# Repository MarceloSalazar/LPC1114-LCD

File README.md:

# LPC1114-LCD

Placa basada en el microcontrolador **NXP LPC1114FN28 (ARM Cortex-M0, DIP-28)** con pantalla **LCD 1602**, LEDs,
pulsadores y buzzer. Su uso principal es un **temporizador Pomodoro**, aunque también sirve como reloj con alarma.
Se programa en C.

**Esquemático:** [docs/hardware/LPC1114-LCD_schematic.pdf](docs/hardware/LPC1114-LCD_schematic.pdf)

| Fase | Contenido | Estado |
|------|-----------|--------|
| 1 | Hardware v1.2: PCB de 2 capas montado por JLCPCB (PCBA) con componentes Basic | Listo para fabricar |
| 1b | Caja impresa en 3D de dos piezas (FreeCAD) | Lista: STEP + STL en [enclosure/](enclosure) |
| 2 | Firmware en C: temporizador Pomodoro / reloj (+ tests) | Pendiente |

## Características (v1.2)

- **MCU**: LPC1114FN28/102, 50 MHz, 32 kB flash, 4 kB RAM, en zócalo DIP-28. La base de tiempos es un cristal de 12 MHz de ±10 ppm.
- **Alimentación**: micro USB (5 V) con protección ESD USBLC6-2SC6 y regulador XC6206 de 3,3 V.
  Si no montas el USBLC6, puenteas con estaño **JP3** y **JP4**.
- **USB-serie**: CH340C en el mismo conector micro USB. Además, pads UART de 1 × 3 (GND, RX, TX) a 3,3 V.
  Con los puentes **JP5** y **JP6** eliges si la UART del MCU va al CH340 (de fábrica) o a J3.
- **Programación**: pads de 1 × 7 (3V3, SWDIO, SWCLK, RESET, GND, SCL, SDA) para un programador CMSIS-DAP.
  Los pines SCL y SDA quedan libres para módulos I2C. También se puede programar con el bootloader ISP por UART,
  de forma automática si se cierran los puentes JP1 y JP2.
- **LCD 1602** en modo 4 bits, montado encima del PCB. El footprint es de 18 pines: 16 estándar más 2 para módulos RGB.
  La retroiluminación se regula por PWM y el contraste con un trimmer multivuelta.
- **Interfaz de usuario**: 4 pulsadores (MODE/ISP, UP, DOWN, OK), RESET, 3 LEDs y LED de encendido,
  y buzzer piezoeléctrico TDK PS1420P02CT.
- **RTC opcional (DNP)**: la cara inferior tiene la huella de un DS3231MZ, su condensador y un portapilas CR2032 SMD, en el bus I2C de J2.
  No se montan; quedan para una ampliación futura.
- **PCB**: **80 × 52 mm**, 2 capas. JLCPCB monta todos los componentes SMD (una sola cara, casi todos Basic).
  Tú sueldas 7 componentes: el LPC1114, el LCD, el trimmer, el buzzer, el USBLC6 y las 2 tiras de pines.

## Estructura del repositorio

```
LPC1114-LCD/
├── hardware/                 Proyecto KiCad 10
│   ├── LPC1114-LCD.kicad_pro/.kicad_sch/.kicad_pcb
│   ├── lib/                  Símbolos y footprints propios
│   ├── fabrication/          Gerber (.zip), BOM + CPL de JLCPCB, soldadura manual, opciones DNP, STEP
│   └── scripts/              export_fab.ps1: ERC/DRC y generación de todos los ficheros
├── enclosure/                Caja 3D (FreeCAD): script paramétrico, STEP y STL
├── firmware/                 Fase 2 (en C)
│   ├── app/                  Aplicación; inc/board.h contiene el mapa de pines
│   ├── lib/                  CMSIS / drivers
│   └── tests/                Tests unitarios
└── docs/
    ├── datasheets/           Hojas de datos
    ├── hardware/             Notas de diseño, revisión para JLCPCB, esquemático en PDF
    └── images/               Renders del PCB y de la caja
```

## Mapa de pines (LPC1114FN28)

| Pin | Puerto | Función en la placa | Notas |
|----:|--------|---------------------|-------|
| 1  | PIO0_8  | BTN_OK (SW4)        | Activo en bajo, pull-up de 10k |
| 2  | PIO0_9  | BTN_UP (SW2)        | Activo en bajo |
| 3  | SWCLK   | SWD (J2-3)          | |
| 4  | PIO0_11 | LCD_BL (PWM CT32B0_MAT3) | Retroiluminación, activo en alto. IOCON FUNC=1 |
| 5  | PIO0_5  | I2C SDA (J2-7)      | Expansión y RTC opcional; pull-up de 4k7 |
| 6  | PIO0_6  | LCD D7              | |
| 9  | PIO1_0  | LCD D6              | IOCON FUNC=1 |
| 10 | PIO1_1  | LCD D5              | IOCON FUNC=1 |
| 11 | PIO1_2  | LCD D4              | IOCON FUNC=1 |
| 12 | SWDIO   | SWD (J2-2)          | |
| 13 | PIO1_4  | LCD E               | |
| 14 | PIO1_5  | LCD RS              | |
| 15 | PIO1_6  | UART RXD            | Desde el CH340 (1k en serie) o J3-2, según JP5 |
| 16 | PIO1_7  | UART TXD            | Hacia el CH340 o J3-3, según JP6 |
| 17 | PIO1_8  | BTN_DOWN (SW3)      | Activo en bajo |
| 18 | PIO1_9  | BUZZER (PWM CT16B1_MAT0) | Activo en alto (NPN hacia el piezo a 5 V) |
| 19/20 | XTALOUT/XTALIN | Cristal de 12 MHz | |
| 23 | RESET   | RESET (SW5, J2-4, CH340 DTR vía JP1) | |
| 24 | PIO0_1  | BTN_MODE (SW1) / ISP | Pulsado durante el reset: arranca el bootloader UART |
| 25 | PIO0_2  | LED1 (rojo)         | Activo en alto |
| 26 | PIO0_3  | LED2 (amarillo)     | Activo en alto |
| 27 | PIO0_4  | I2C SCL (J2-6)      | Expansión y RTC opcional; pull-up de 4k7 |
| 28 | PIO0_7  | LED3 (verde)        | Activo en alto |

El LCD tiene R/W a GND (solo escritura) y se controla con lógica de 3,3 V. Este mapa también está en
[firmware/app/inc/board.h](firmware/app/inc/board.h).

## Fabricación y montaje en JLCPCB

1. En <https://jlcpcb.com>, sube [hardware/fabrication/LPC1114-LCD_JLCPCB.zip](hardware/fabrication/LPC1114-LCD_JLCPCB.zip)
   y elige 2 capas, 1,6 mm, HASL y el color que quieras.
   En *Remove Order Number* selecciona **Specify a location**: JLCPCB pone el número en la cara inferior, donde está el texto `JLCJLCJLCJLC`.
2. Activa **PCB Assembly**, en cara superior (*Top side*), y sube:
   - BOM: [LPC1114-LCD_JLCPCB_BOM.csv](hardware/fabrication/LPC1114-LCD_JLCPCB_BOM.csv) (24 líneas, cada una con su código LCSC).
   - CPL: [LPC1114-LCD_JLCPCB_CPL.csv](hardware/fabrication/LPC1114-LCD_JLCPCB_CPL.csv).
3. Antes de confirmar, **revisa la orientación de cada pieza** en la vista previa de JLCPCB. Presta especial atención a los SOT-23, SOIC-16, cristal,
   micro USB y pulsadores; si alguno aparece girado, corrígelo ahí mismo.
4. La lista de componentes que sueldas tú está en [LPC1114-LCD_hand_solder.csv](hardware/fabrication/LPC1114-LCD_hand_solder.csv).
   Los componentes opcionales (DNP) del RTC están en [LPC1114-LCD_DNP_options.csv](hardware/fabrication/LPC1114-LCD_DNP_options.csv).

### Puentes de soldadura

| Puente | De fábrica | Qué hacer |
|--------|------------|-----------|
| JP1 / JP2 | Abiertos | Ciérralos para que el CH340 controle RESET e ISP (`lpc21isp -control`) |
| JP3 / JP4 | Abiertos | Ciérralos **solo si no montas el USBLC6 (U5)** |
| JP5 / JP6 | 1-2 puenteado (CH340) | Para usar una UART externa en J3: corta la pista 1-2 y puentea 2-3 en los dos |

Detalles, tipo de cada componente y decisiones:
[docs/hardware/design-notes.md](docs/hardware/design-notes.md) y
[docs/hardware/schematic-review-jlcpcb.md](docs/hardware/schematic-review-jlcpcb.md).

Para regenerar los ficheros después de modificar el diseño en KiCad:

```powershell
powershell -ExecutionPolicy Bypass -File hardware\scripts\export_fab.ps1
```

## Caja

Dos piezas, la superior con el display y la inferior como base, de **92,8 × 64,8 × 31,4 mm**, unidas con 4 tornillos M3 × 16 desde abajo.
Los pulsadores van integrados en la tapa y los LEDs se ven a través de guías de luz de metacrilato de Ø3 mm.
Detalles, impresión y tornillería en [enclosure/README.md](enclosure/README.md).

## Programación (fase 2)

- **SWD**: conecta un programador CMSIS-DAP a J2 y usa [pyOCD](https://pyocd.io) (`pyocd flash -t lpc1114fn28 app.hex`) u OpenOCD.
- **UART ISP**: mantén MODE pulsado, pulsa RESET y usa `lpc21isp` o Flash Magic en el puerto COM del CH340.
  Con JP1 y JP2 cerrados con estaño, `lpc21isp -control` lo hace solo.

## Licencia

[MIT](LICENSE): hardware, firmware y documentación de este repositorio. Las hojas de datos de `docs/datasheets/` pertenecen a sus fabricantes.

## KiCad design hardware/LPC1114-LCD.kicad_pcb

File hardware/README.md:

# Hardware: proyecto KiCad 10

| Fichero | Contenido |
|---------|-----------|
| `LPC1114-LCD.kicad_pro` | Proyecto: clases de red (Default 0,25 mm; Power 0,3 mm para GND, +3V3, retroiluminación y buzzer) y reglas |
| `LPC1114-LCD.kicad_sch` | Esquemático (una hoja A3, organizada en bloques) |
| `LPC1114-LCD.kicad_pcb` | PCB de 2 capas, 80 × 52 mm (v1.2); RTC opcional y puentes en la cara inferior |
| `lib/LPC1114-LCD.kicad_sym` | Símbolos propios: `LPC1114FN28` (DIP-28), `LCD1602` (18 pines), `CH340C` (V3 como entrada de alimentación) |
| `lib/LPC1114-LCD.pretty/` | Footprints propios: `LCD1602_18pin` (fila de 1 × 18, taladros M2.5 de 75 × 31 mm), `SW_TS-1187A_5.1x5.1mm` (pulsador SMD) y `Buzzer_TDK_PS1420P02CT_D14mm_P10mm` |
| `fabrication/` | Gerber para JLCPCB (`.zip`), **BOM y CPL de PCBA** (`*_JLCPCB_BOM.csv`, `*_JLCPCB_CPL.csv`), lista de soldadura manual (`*_hand_solder.csv`), BOM completa y modelo 3D (`.step`) |
| `scripts/export_fab.ps1` | ERC y DRC, y exportación de todos los ficheros de fabricación y documentación |

Las librerías del proyecto se referencian con `${KIPRJMOD}` en `sym-lib-table` y `fp-lib-table`, así que el proyecto
se abre directamente sin configurar nada. El resto de símbolos, footprints y modelos 3D son los estándar de KiCad 10.

## Flujo de trabajo

1. Edita el esquemático y el PCB en KiCad.
2. En el PCB: *Herramientas → Actualizar PCB desde el esquemático* (F8) y vuelve a rellenar las zonas (B).
3. Ejecuta el script desde la raíz del repositorio:

   ```powershell
   powershell -ExecutionPolicy Bypass -File hardware\scripts\export_fab.ps1
   ```

   El script se detiene si el ERC o el DRC encuentran errores. Si todo es correcto, regenera
   `fabrication/LPC1114-LCD_JLCPCB.zip`, la BOM y la CPL de JLCPCB, la lista de soldadura manual, el STEP, el PDF del
   esquemático y los renders de `docs/images`.

## Campos de los símbolos

- `LCSC`: código de la pieza en JLCPCB/LCSC. Los símbolos que lo tienen los monta JLCPCB y entran en la BOM y la CPL de PCBA.
- `Assembly = USER`: componentes que se sueldan a mano (U1, DS1, RV1, BZ1, U5, J2, J3).
- **DNP** (atributo *Do Not Populate* y `Assembly = DNP ...`): RTC opcional U4, C9 y BT1 en la cara inferior.
  No entran en la BOM ni la CPL de JLCPCB; el script los lista en `fabrication/LPC1114-LCD_DNP_options.csv`.

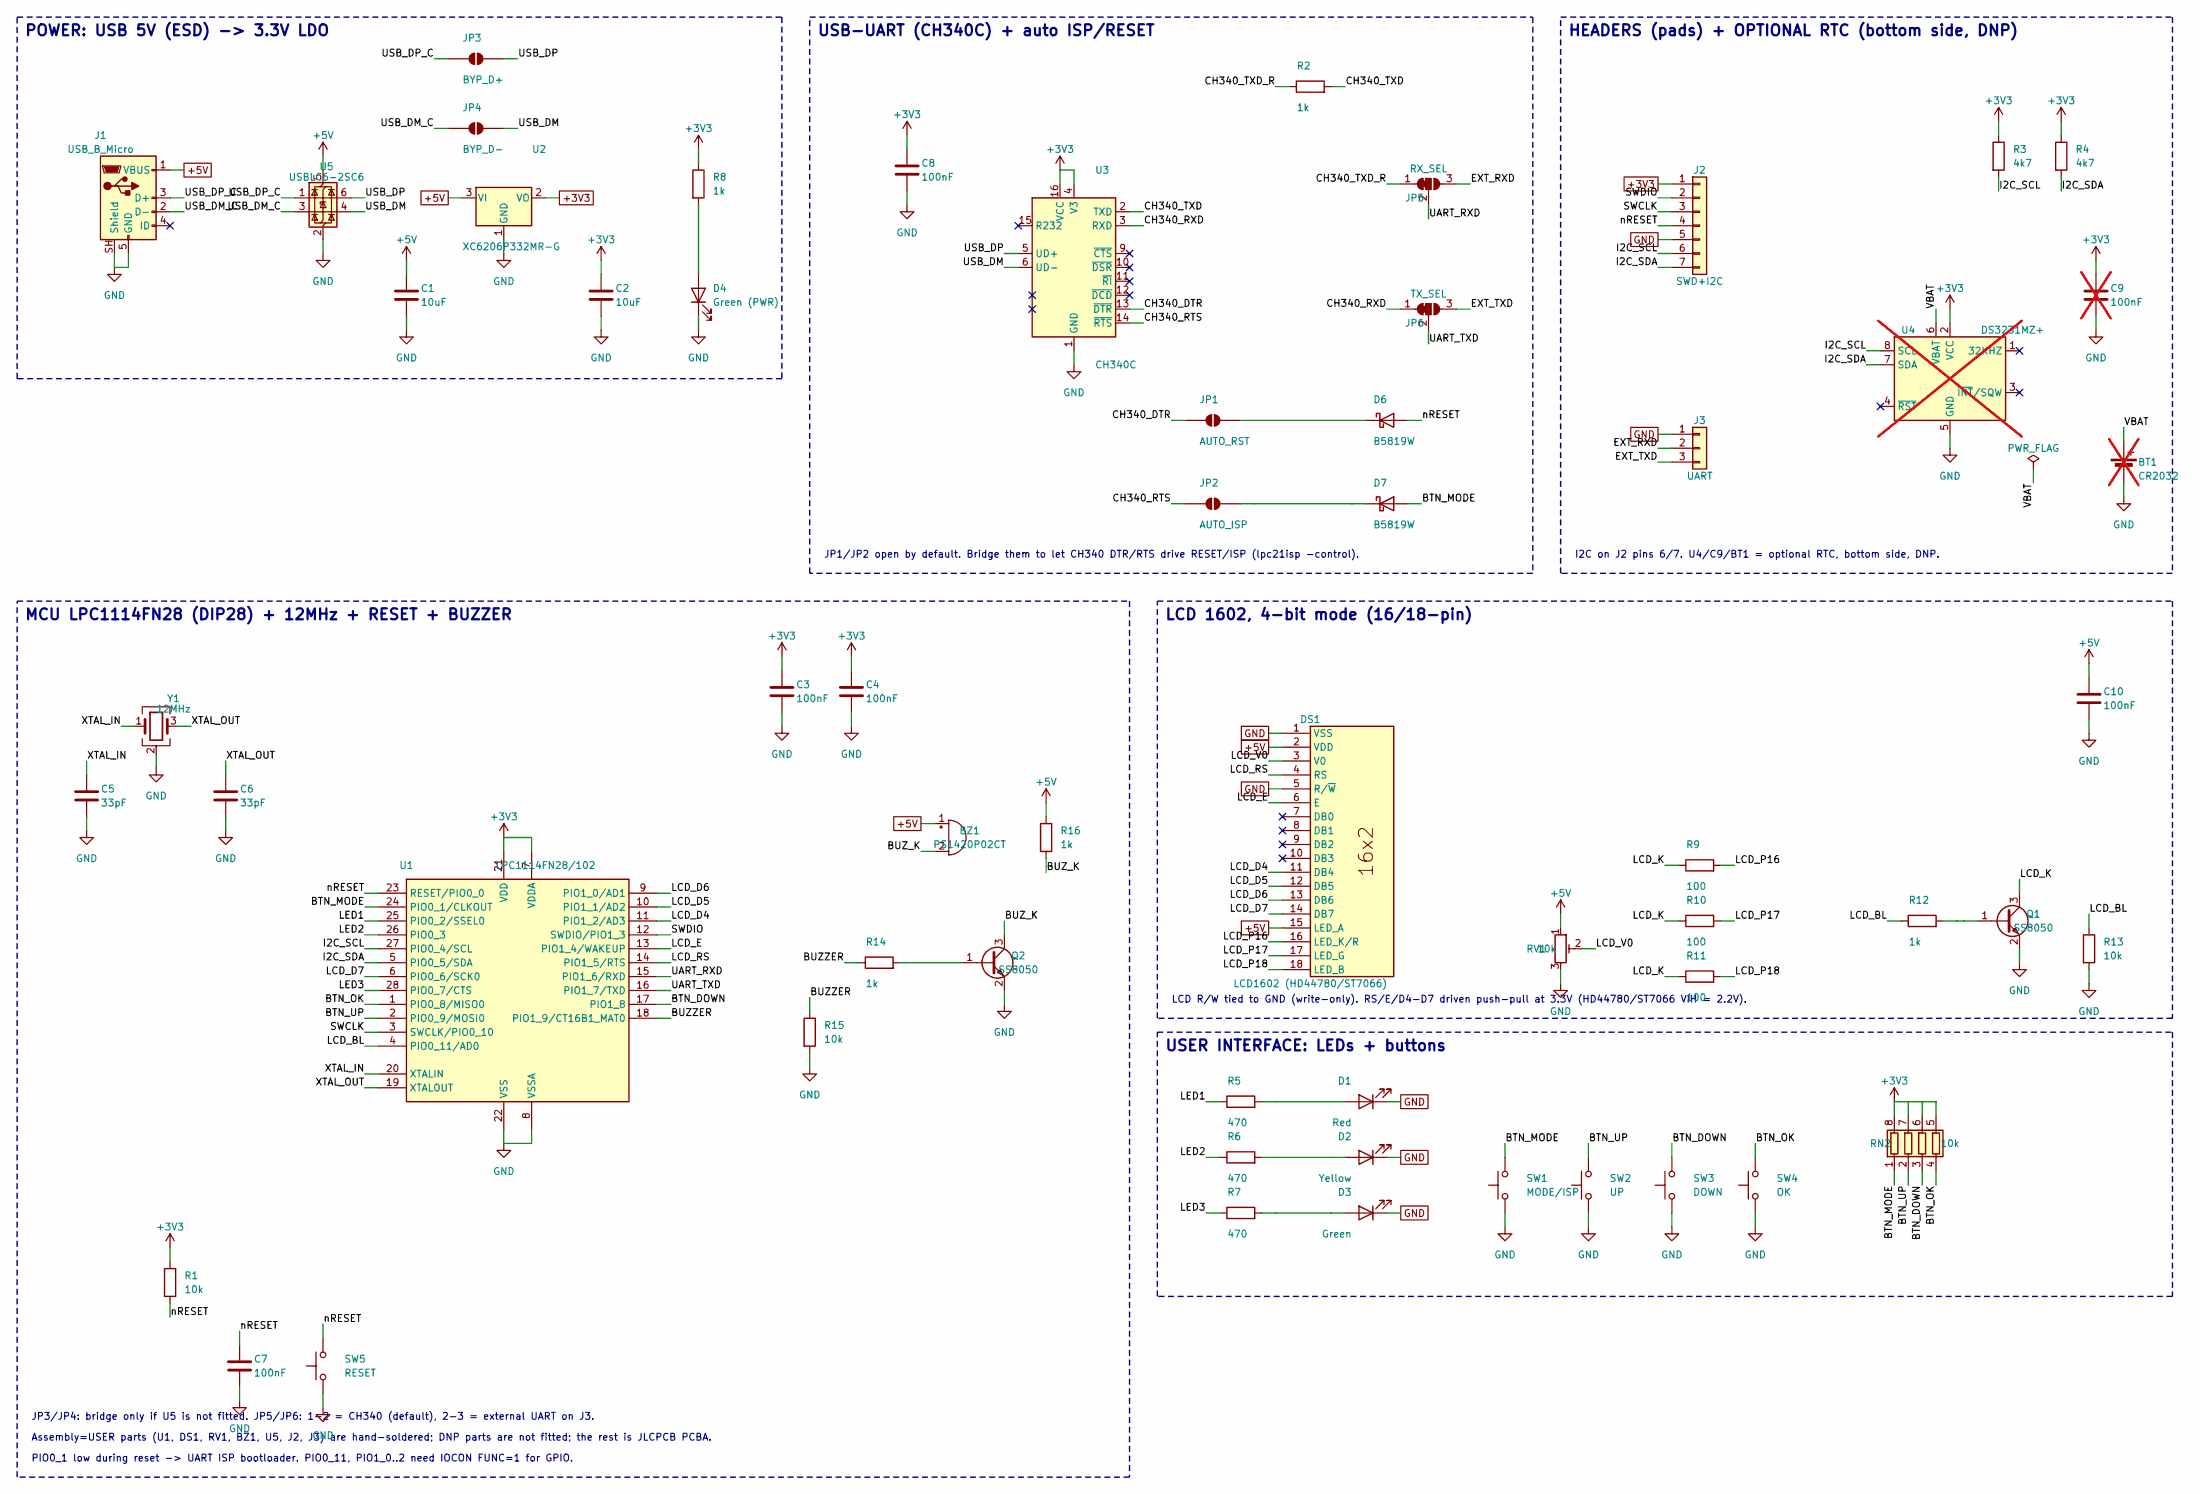
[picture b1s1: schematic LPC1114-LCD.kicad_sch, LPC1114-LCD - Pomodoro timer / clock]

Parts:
BT1: CR2032; BatteryHolder_Keystone_3034_1x20mm; MPN Keystone 3034 (SMD CR2032 holder); LCSC C5213768; not fitted
BZ1: PS1420P02CT; Buzzer_TDK_PS1420P02CT_D14mm_P10mm; MPN TDK PS1420P02CT (piezo, D14 mm, pitch 1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
C1, C2: 10uF; C_0805_2012Metric; LCSC C15850
C3, C4, C7, C8, C10: 100nF; C_0603_1608Metric; LCSC C14663
C5, C6: 33pF; C_0603_1608Metric; LCSC C1663
C9: 100nF; C_0603_1608Metric; LCSC C14663; not fitted
D1: Red; LED_0805_2012Metric; LCSC C84256
D2: Yellow; LED_0805_2012Metric; LCSC C2296
D3: Green; LED_0805_2012Metric; LCSC C2297
D4: Green (PWR); LED_0805_2012Metric; LCSC C2297
D6, D7: B5819W; D_SOD-123; LCSC C8598
DS1: LCD1602 (HD44780/ST7066); LCD1602_18pin
J1: USB_B_Micro; USB_Micro-B_XKB_U254-051T-4BH83-F1S; MPN XKB U254-051T-4BH83-F1S; LCSC C397452
J2: SWD+I2C; PinHeader_1x07_P2.54mm_Vertical
J3: UART; PinHeader_1x03_P2.54mm_Vertical
JP1: AUTO_RST; SolderJumper-2_P1.3mm_Open_Pad1.0x1.5mm
JP2: AUTO_ISP; SolderJumper-2_P1.3mm_Open_Pad1.0x1.5mm
JP3: BYP_D+; SolderJumper-2_P1.3mm_Open_Pad1.0x1.5mm
JP4: BYP_D-; SolderJumper-2_P1.3mm_Open_Pad1.0x1.5mm
JP5: RX_SEL; SolderJumper-3_P1.3mm_Bridged12_Pad1.0x1.5mm
JP6: TX_SEL; SolderJumper-3_P1.3mm_Bridged12_Pad1.0x1.5mm
Q1, Q2: SS8050; SOT-23; LCSC C2150
R1, R13, R15: 10k; R_0603_1608Metric; LCSC C25804
R2, R8, R12, R14, R16: 1k; R_0603_1608Metric; LCSC C21190
R3, R4: 4k7; R_0603_1608Metric; LCSC C23162
R5, R6, R7: 470; R_0603_1608Metric; LCSC C23179
R9, R10, R11: 100; R_0603_1608Metric; LCSC C22775
RN2: 10k; R_Array_Convex_4x0603; LCSC C29718
RV1: 10k; Potentiometer_Bourns_3296W_Vertical
SW1: MODE/ISP; SW_TS-1187A_5.1x5.1mm; LCSC C318884
SW2: UP; SW_TS-1187A_5.1x5.1mm; LCSC C318884
SW3: DOWN; SW_TS-1187A_5.1x5.1mm; LCSC C318884
SW4: OK; SW_TS-1187A_5.1x5.1mm; LCSC C318884
SW5: RESET; SW_TS-1187A_5.1x5.1mm; LCSC C318884
U1: LPC1114FN28/102; DIP-28_W15.24mm_Socket; MPN NXP LPC1114FN28/102 + DIP-28 600mil soc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
U2: XC6206P332MR-G; SOT-23; MPN Torex XC6206P332MR-G; LCSC C5446
U3: CH340C; SOIC-16_3.9x9.9mm_P1.27mm; MPN WCH CH340C (SOIC-16, no crystal); LCSC C84681
U4: DS3231MZ+; SOIC-8_3.9x4.9mm_P1.27mm; MPN Analog Devices DS3231MZ+ (+-5ppm MEMS R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; LCSC C107410; not fitted
U5: USBLC6-2SC6; SOT-23-6_Handsoldering; MPN ST USBLC6-2SC6
Y1: 12MHz; Crystal_SMD_3225-4Pin_3.2x2.5mm; MPN YXC X322512MSB4SI 12MHz CL=20pF; LCSC C9002

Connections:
+3V3: C2.1, C3.1, C4.1, C8.1, C9.1, J2.1, R1.1, R3.1, R4.1, R8.1, RN2.5 (R4.2), RN2.6 (R3.2), RN2.7 (R2.2), RN2.8 (R1.2), U1.7 (VDDA), U1.21 (VDD), U2.2 (VO), U3.4 (V3), U3.16 (VCC), U4.2 (VCC)
+5V: BZ1.1 (+), C1.1, C10.1, DS1.2 (VDD), DS1.15 (LED_A), J1.1 (VBUS), R16.1, RV1.1, U2.3 (VI), U5.5 (VBUS)
/BTN_DOWN: RN2.3 (R3.1), SW3.2, U1.17 (PIO1_8)
/BTN_MODE: D7.2 (A), RN2.1 (R1.1), SW1.2, U1.24 (PIO0_1/CLKOUT)
/BTN_OK: RN2.4 (R4.1), SW4.2, U1.1 (PIO0_8/MISO0)
/BTN_UP: RN2.2 (R2.1), SW2.2, U1.2 (PIO0_9/MOSI0)
/BUZZER: R14.1, R15.1, U1.18 (PIO1_9/CT16B1_MAT0)
/BUZ_K: BZ1.2 (-), Q2.3 (C), R16.2
/CH340_DTR: JP1.1 (A), U3.13 (~DTR)
/CH340_RTS: JP2.1 (A), U3.14 (~RTS)
/CH340_RXD: JP6.1 (A), U3.3 (RXD)
/CH340_TXD: R2.2, U3.2 (TXD)
/CH340_TXD_R: JP5.1 (A), R2.1
/EXT_RXD: J3.2, JP5.3 (B)
/EXT_TXD: J3.3, JP6.3 (B)
/I2C_SCL: J2.6, R3.2, U1.27 (PIO0_4/SCL), U4.8 (SCL)
/I2C_SDA: J2.7, R4.2, U1.5 (PIO0_5/SDA), U4.7 (SDA)
/LCD_BL: R12.1, R13.1, U1.4 (PIO0_11/AD0)
/LCD_D4: DS1.11 (DB4), U1.11 (PIO1_2/AD3)
/LCD_D5: DS1.12 (DB5), U1.10 (PIO1_1/AD2)
/LCD_D6: DS1.13 (DB6), U1.9 (PIO1_0/AD1)
/LCD_D7: DS1.14 (DB7), U1.6 (PIO0_6/SCK0)
/LCD_E: DS1.6 (E), U1.13 (PIO1_4/WAKEUP)
/LCD_K: Q1.3 (C), R9.1, R10.1, R11.1
/LCD_P16: DS1.16 (LED_K/R), R9.2
/LCD_P17: DS1.17 (LED_G), R10.2
/LCD_P18: DS1.18 (LED_B), R11.2
/LCD_RS: DS1.4 (RS), U1.14 (PIO1_5/RTS)
/LCD_V0: DS1.3 (V0), RV1.2
/LED1: R5.1, U1.25 (PIO0_2/SSEL0)
/LED2: R6.1, U1.26 (PIO0_3)
/LED3: R7.1, U1.28 (PIO0_7/CTS)
/SWCLK: J2.3, U1.3 (SWCLK/PIO0_10)
/SWDIO: J2.2, U1.12 (SWDIO/PIO1_3)
/UART_RXD: JP5.2 (C), U1.15 (PIO1_6/RXD)
/UART_TXD: JP6.2 (C), U1.16 (PIO1_7/TXD)
/USB_DM: JP4.2 (B), U3.6 (UD-), U5.4 (I/O2)
/USB_DM_C: J1.2 (D-), JP4.1 (A), U5.3 (I/O2)
/USB_DP: JP3.2 (B), U3.5 (UD+), U5.6 (I/O1)
/USB_DP_C: J1.3 (D+), JP3.1 (A), U5.1 (I/O1)
/VBAT: BT1.1 (+), U4.6 (VBAT)
/XTAL_IN: C5.1, U1.20 (XTALIN), Y1.1
/XTAL_OUT: C6.1, U1.19 (XTALOUT), Y1.3
/nRESET: C7.1, D6.2 (A), J2.4, R1.2, SW5.2, U1.23 (RESET/PIO0_0)
GND: BT1.2 (-), C1.2, C2.2, C3.2, C4.2, C5.2, C6.2, C7.2, C8.2, C9.2, C10.2, D1.1 (K), D2.1 (K), D3.1 (K), D4.1 (K), DS1.1 (VSS), DS1.5 (R/~W), J1.5 (GND), J1.SH (Shield), J2.5, J3.1, Q1.2 (E), Q2.2 (E), R13.2, R15.2, RV1.3, SW1.1, SW2.1, SW3.1, SW4.1, SW5.1, U1.8 (VSSA), U1.22 (VSS), U2.1 (GND), U3.1 (GND), U4.5 (GND), U5.2 (GND), Y1.2 (G), Y1.4 (G)
unnamed: D1.2 (A), R5.2
unnamed: D2.2 (A), R6.2
unnamed: D3.2 (A), R7.2
unnamed: D4.2 (A), R8.2
unnamed: D6.1 (K), JP1.2 (B)
unnamed: D7.1 (K), JP2.2 (B)
unnamed: Q1.1 (B), R12.2
unnamed: Q2.1 (B), R14.2

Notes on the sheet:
POWER: USB 5V (ESD) -> 3.3V LDO
USB-UART (CH340C) + auto ISP/RESET
HEADERS (pads) + OPTIONAL RTC (bottom side, DNP)
MCU LPC1114FN28 (DIP28) + 12MHz + RESET + BUZZER
LCD 1602, 4-bit mode (16/18-pin)
USER INTERFACE: LEDs + buttons
JP1/JP2 open by default. Bridge them to let CH340 DTR/RTS drive RESET/ISP (lpc21isp -control).
LCD R/W tied to GND (write-only). RS/E/D4-D7 driven push-pull at 3.3V (HD44780/ST7066 VIH = 2.2V).
PIO0_1 low during reset -> UART ISP bootloader. PIO0_11, PIO1_0..2 need IOCON FUNC=1 for GPIO.
Assembly=USER parts (U1, DS1, RV1, BZ1, U5, J2, J3) are hand-soldered; DNP parts are not fitted; the rest is JLCPCB PCBA.
I2C on J2 pins 6/7. U4/C9/BT1 = optional RTC, bottom side, DNP.
JP3/JP4: bridge only if U5 is not fitted. JP5/JP6: 1-2 = CH340 (default), 2-3 = external UART on J3.

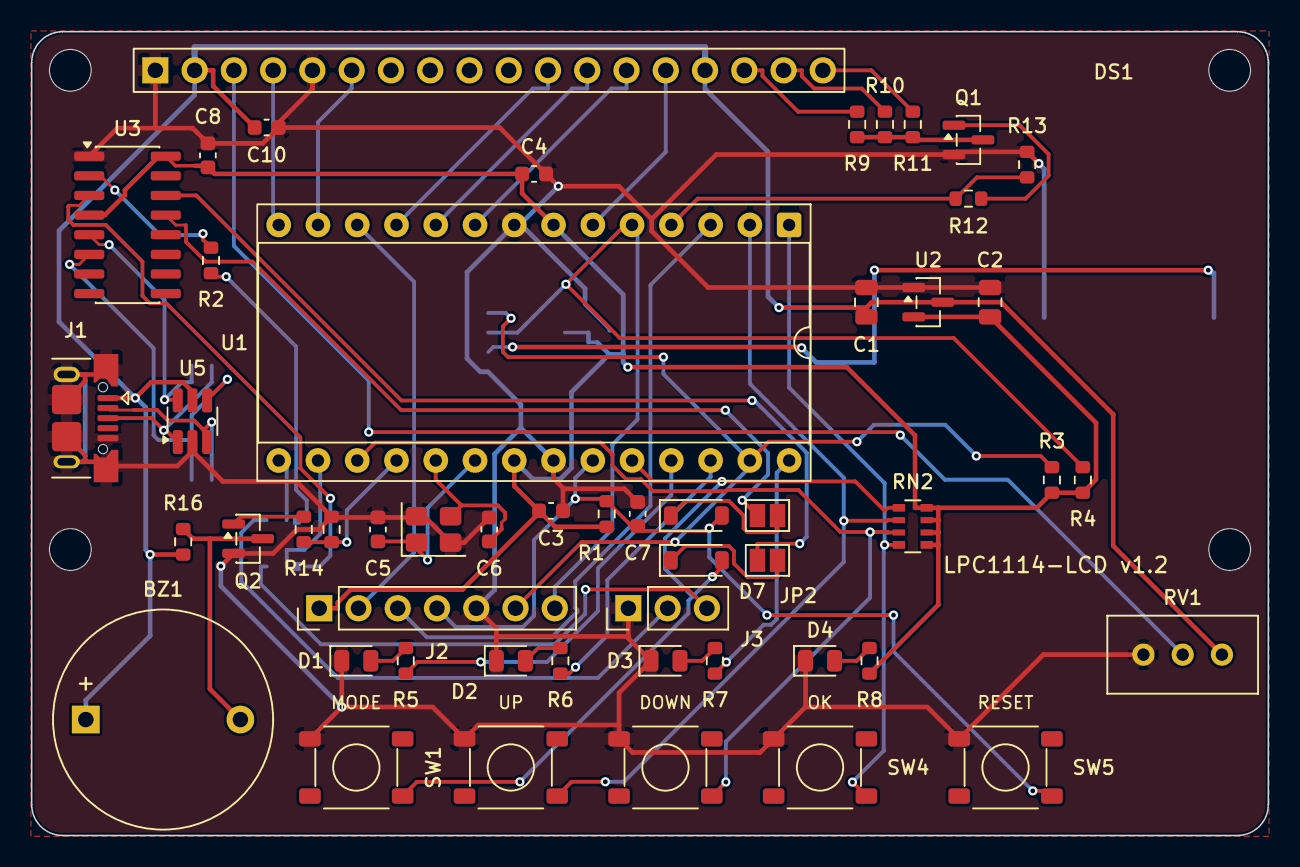
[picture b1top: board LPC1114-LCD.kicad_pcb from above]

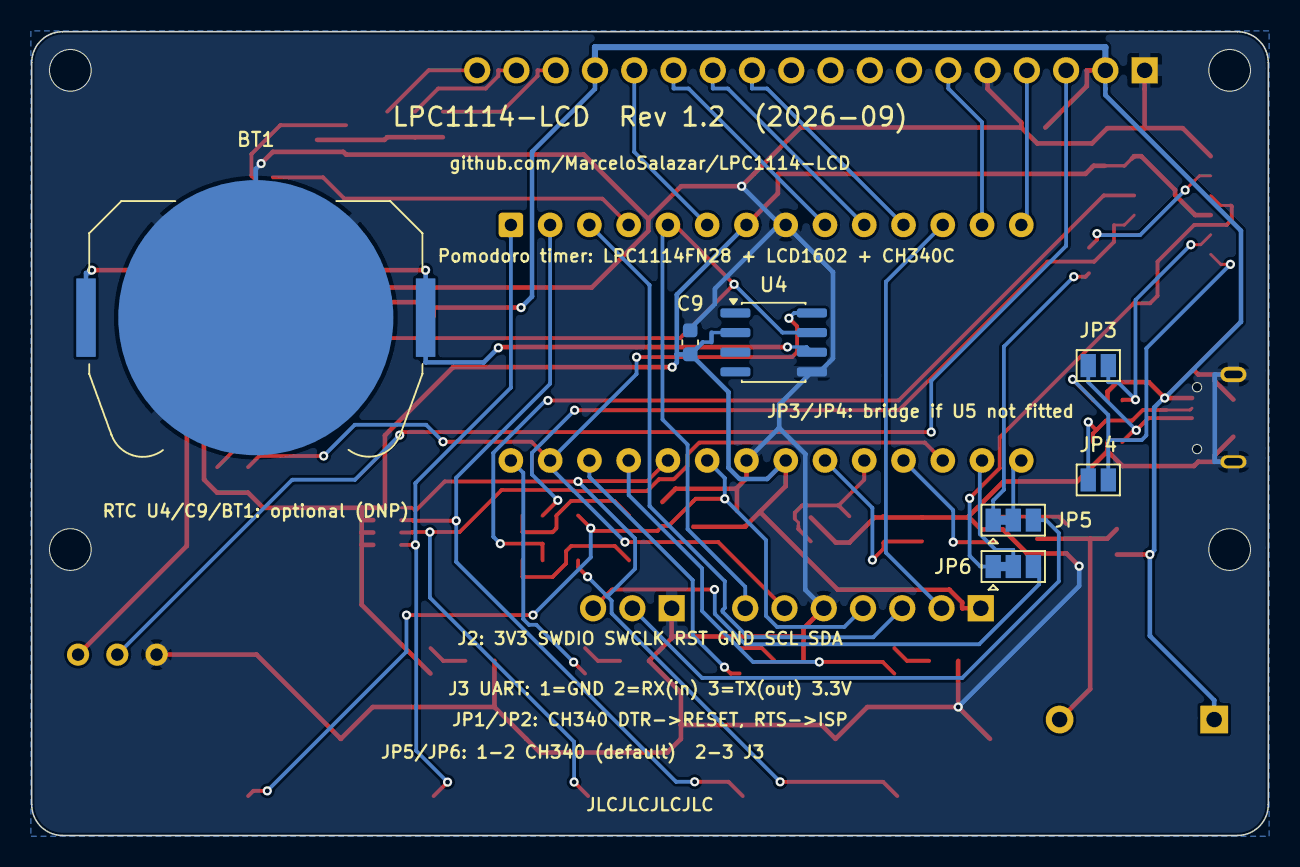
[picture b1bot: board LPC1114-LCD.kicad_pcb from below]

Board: 2 copper layers, 80.0 x 52.0 mm, 59 parts (7 on the bottom side), 53 nets.

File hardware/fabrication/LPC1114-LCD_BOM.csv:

"Reference","Value","Footprint","Qty","LCSC","Assembly","MPN","Description"
"BZ1","PS1420P02CT","LPC1114-LCD:Buzzer_TDK_PS1420P02CT_D14mm_P10mm","1","","USER","TDK PS1420P02CT (piezo, D14 mm, pitch 10 mm)","Buzzer, polarized"
"C1,C2","10uF","Capacitor_SMD:C_0805_2012Metric","2","C15850","","","Unpolarized capacitor"
"C3,C4,C7,C8,C10","100nF","Capacitor_SMD:C_0603_1608Metric","5","C14663","","","Unpolarized capacitor,VDD decoupling,VDDA decoupling"
"C5,C6","33pF","Capacitor_SMD:C_0603_1608Metric","2","C1663","","","Unpolarized capacitor"
"D1","Red","LED_SMD:LED_0805_2012Metric","1","C84256","","","Light emitting diode"
"D2","Yellow","LED_SMD:LED_0805_2012Metric","1","C2296","","","Light emitting diode"
"D3","Green","LED_SMD:LED_0805_2012Metric","1","C2297","","","Light emitting diode"
"D4","Green (PWR)","LED_SMD:LED_0805_2012Metric","1","C2297","","","Light emitting diode"
"D6,D7","B5819W","Diode_SMD:D_SOD-123","2","C8598","","","Schottky diode"
"DS1","LCD1602 (HD44780/ST7066)","LPC1114-LCD:LCD1602_18pin","1","","USER","","Mounted on top with 1x16/1x18 female header (user)"
"J1","USB_B_Micro","Connector_USB:USB_Micro-B_XKB_U254-051T-4BH83-F1S","1","C397452","","XKB U254-051T-4BH83-F1S","Micro USB B receptacle: power + USB-UART"
"J2","SWD+I2C","Connector_PinHeader_2.54mm:PinHeader_1x07_P2.54mm_Vertical","1","","USER","","Debug/expansion: 1=3V3 2=SWDIO 3=SWCLK 4=RESET 5=GND 6=SCL 7=SDA"
"J3","UART","Connector_PinHeader_2.54mm:PinHeader_1x03_P2.54mm_Vertical","1","","USER","","External 3.3V UART: GND / RX(in) / TX(out), select with JP5/JP6"
"Q1,Q2","SS8050","Package_TO_SOT_SMD:SOT-23","2","C2150","","","NPN transistor, base/emitter/collector"
"R1,R13,R15","10k","Resistor_SMD:R_0603_1608Metric","3","C25804","","","Resistor"
"R2,R8,R12,R14,R16","1k","Resistor_SMD:R_0603_1608Metric","5","C21190","","","Piezo discharge resistor,Resistor"
"R3,R4","4k7","Resistor_SMD:R_0603_1608Metric","2","C23162","","","Resistor"
"R5-R7","470","Resistor_SMD:R_0603_1608Metric","3","C23179","","","Resistor"
"R9-R11","100","Resistor_SMD:R_0603_1608Metric","3","C22775","","","Backlight Blue (18-pin only),Backlight Green (18-pin only),Backlight K (16-pin) / Red (18-pin)"
"RN2","10k","Resistor_SMD:R_Array_Convex_4x0603","1","C29718","","","4 resistor network, parallel topology"
"RV1","10k","Potentiometer_THT:Potentiometer_Bourns_3296W_Vertical","1","","USER","","LCD contrast, multi-turn vertical trimmer 3 pins in line 2.54 mm (user)"
"SW1","MODE/ISP","LPC1114-LCD:SW_TS-1187A_5.1x5.1mm","1","C318884","","","Push button switch, generic, two pins"
"SW2","UP","LPC1114-LCD:SW_TS-1187A_5.1x5.1mm","1","C318884","","","Push button switch, generic, two pins"
"SW3","DOWN","LPC1114-LCD:SW_TS-1187A_5.1x5.1mm","1","C318884","","","Push button switch, generic, two pins"
"SW4","OK","LPC1114-LCD:SW_TS-1187A_5.1x5.1mm","1","C318884","","","Push button switch, generic, two pins"
"SW5","RESET","LPC1114-LCD:SW_TS-1187A_5.1x5.1mm","1","C318884","","","Push button switch, generic, two pins"
"U1","LPC1114FN28/102","Package_DIP:DIP-28_W15.24mm_Socket","1","","USER","NXP LPC1114FN28/102 + DIP-28 600mil socket","NXP LPC1114 ARM Cortex-M0 MCU, 32kB flash, 4kB SRAM, DIP-28 (LPC1114FN28/102)"
"U2","XC6206P332MR-G","Package_TO_SOT_SMD:SOT-23","1","C5446","","Torex XC6206P332MR-G","Positive 60-250mA Low Dropout Regulator, Fixed Output, SOT-23"
"U3","CH340C","Package_SO:SOIC-16_3.9x9.9mm_P1.27mm","1","C84681","","WCH CH340C (SOIC-16, no crystal)","USB serial converter, SOIC-16. Project copy: V3 pin typed power_in because V3 is tied to VCC for 3.3V operation"
"U5","USBLC6-2SC6","Package_TO_SOT_SMD:SOT-23-6_Handsoldering","1","","USER","ST USBLC6-2SC6","USB ESD protection (hand-soldered by the user)"
"Y1","12MHz","Crystal:Crystal_SMD_3225-4Pin_3.2x2.5mm","1","C9002","","YXC X322512MSB4SI 12MHz CL=20pF","Four pin crystal, GND on pins 2 and 4"

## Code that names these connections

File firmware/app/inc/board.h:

/*
 * board.h - LPC1114-LCD v1.2 pin map and board constants.
 *
 * Generated from the hardware design (hardware/LPC1114-LCD.kicad_sch).
 * Keep in sync with the schematic whenever the hardware changes.
 */
#ifndef BOARD_H
#define BOARD_H

/* ---------------------------------------------------------------- Clocks */
#define BOARD_XTAL_HZ           12000000UL  /* Y1, system oscillator (XTALIN/XTALOUT) */
#define BOARD_CORE_CLOCK_HZ     48000000UL  /* 12 MHz x 4 via system PLL */

/* ---------------------------------------------------------------- Pin convention
 * Each signal is described by its GPIO port (0/1) and bit number.
 * NOTE: PIO0_11, PIO1_0, PIO1_1 and PIO1_2 start in a reserved function after
 * reset: their IOCON register must select FUNC = 1 (GPIO) and digital mode (ADMODE = 1).
 */

/* ---------------------------------------------------------------- LCD 1602 (4-bit, write only: R/W tied to GND)
 * Driven push-pull at 3.3 V (HD44780/ST7066 VIH = 2.2 V). No external pull-ups.
 */
#define LCD_RS_PORT             1
#define LCD_RS_PIN              5   /* PIO1_5, DIP pin 14 */
#define LCD_E_PORT              1
#define LCD_E_PIN               4   /* PIO1_4, DIP pin 13 */
#define LCD_D4_PORT             1
#define LCD_D4_PIN              2   /* PIO1_2, DIP pin 11 (IOCON FUNC=1) */
#define LCD_D5_PORT             1
#define LCD_D5_PIN              1   /* PIO1_1, DIP pin 10 (IOCON FUNC=1) */
#define LCD_D6_PORT             1
#define LCD_D6_PIN              0   /* PIO1_0, DIP pin 9  (IOCON FUNC=1) */
#define LCD_D7_PORT             0
#define LCD_D7_PIN              6   /* PIO0_6, DIP pin 6 */

/* Backlight: NPN low-side switch, active high. PWM on CT32B0_MAT3 (IOCON FUNC=3). */
#define LCD_BL_PORT             0
#define LCD_BL_PIN              11  /* PIO0_11, DIP pin 4 (IOCON FUNC=1 for GPIO) */

/* ---------------------------------------------------------------- Buttons (active low, 10k external pull-ups) */
#define BTN_MODE_PORT           0
#define BTN_MODE_PIN            1   /* PIO0_1, DIP pin 24 - held low at reset = UART ISP */
#define BTN_UP_PORT             0
#define BTN_UP_PIN              9   /* PIO0_9, DIP pin 2 */
#define BTN_DOWN_PORT           1
#define BTN_DOWN_PIN            8   /* PIO1_8, DIP pin 17 */
#define BTN_OK_PORT             0
#define BTN_OK_PIN              8   /* PIO0_8, DIP pin 1 */

/* ---------------------------------------------------------------- LEDs (active high, 470R) */
#define LED1_PORT               0
#define LED1_PIN                2   /* PIO0_2, DIP pin 25 - red */
#define LED2_PORT               0
#define LED2_PIN                3   /* PIO0_3, DIP pin 26 - yellow */
#define LED3_PORT               0
#define LED3_PIN                7   /* PIO0_7, DIP pin 28 - green (high-current pin) */

/* ---------------------------------------------------------------- Buzzer (TDK PS1420P02CT piezo, ~2 kHz resonance)
 * NPN low side on 5 V, active high. PWM on CT16B1_MAT0 (IOCON FUNC=1).
 * 10k pull-down keeps it off during reset.
 */
#define BUZZER_PORT             1
#define BUZZER_PIN              9   /* PIO1_9, DIP pin 18 */
#define BUZZER_RESONANCE_HZ     2000UL

/* ---------------------------------------------------------------- I2C on J2 pins 6/7 (4k7 pull-ups to 3.3 V)
 * Optional RTC footprint on the bottom side (DS3231MZ, DNP by default).
 */
#define I2C_SCL_PORT            0
#define I2C_SCL_PIN             4   /* PIO0_4, DIP pin 27 */
#define I2C_SDA_PORT            0
#define I2C_SDA_PIN             5   /* PIO0_5, DIP pin 5 */
#define RTC_I2C_ADDR            0x68U   /* only if the optional DS3231MZ (U4) is fitted */

/* ---------------------------------------------------------------- UART
 * Routed to the CH340C (micro USB) by default, or to header J3 by re-bridging JP5/JP6 (2-3).
 */
#define UART_RXD_PORT           1
#define UART_RXD_PIN            6   /* PIO1_6, DIP pin 15 */
#define UART_TXD_PORT           1
#define UART_TXD_PIN            7   /* PIO1_7, DIP pin 16 */
#define UART_DEFAULT_BAUD       115200UL

#endif /* BOARD_H */
